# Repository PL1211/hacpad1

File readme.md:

XIAO RP2040 6-Key Macropad BOM

A simple 6-button macropad with rotary encoder, RGB LEDs, and OLED display running KMK firmware on CircuitPython. I made this to control my music easier with play/pause buttons and volume up, down, and mute.

1x Seeed XIAO RP2040

1x Header pins for the XIAO (usually included, do NOT solder the board flat)

6x Mechanical Switches (MX-Style)

1x EC11 Rotary Encoder (5-pin)

1x Knob for Encoder

6x Blank DSA Keycaps (White)

1x 0.91" OLED Display (Pin order must be GND-VCC-SCL-SDA)

6x SK6812 MINI-E LEDs (Reverse mount with legs)

7x 1N4148 Diodes (Through-Hole)

1x 3D Printed Case (PLA/PETG, not Acrylic)

4x M3 x 16mm Screws

4x M3 Heat-Set Inserts (M3x5mmx4mm)

Wire (24-28 AWG)

## Pictures

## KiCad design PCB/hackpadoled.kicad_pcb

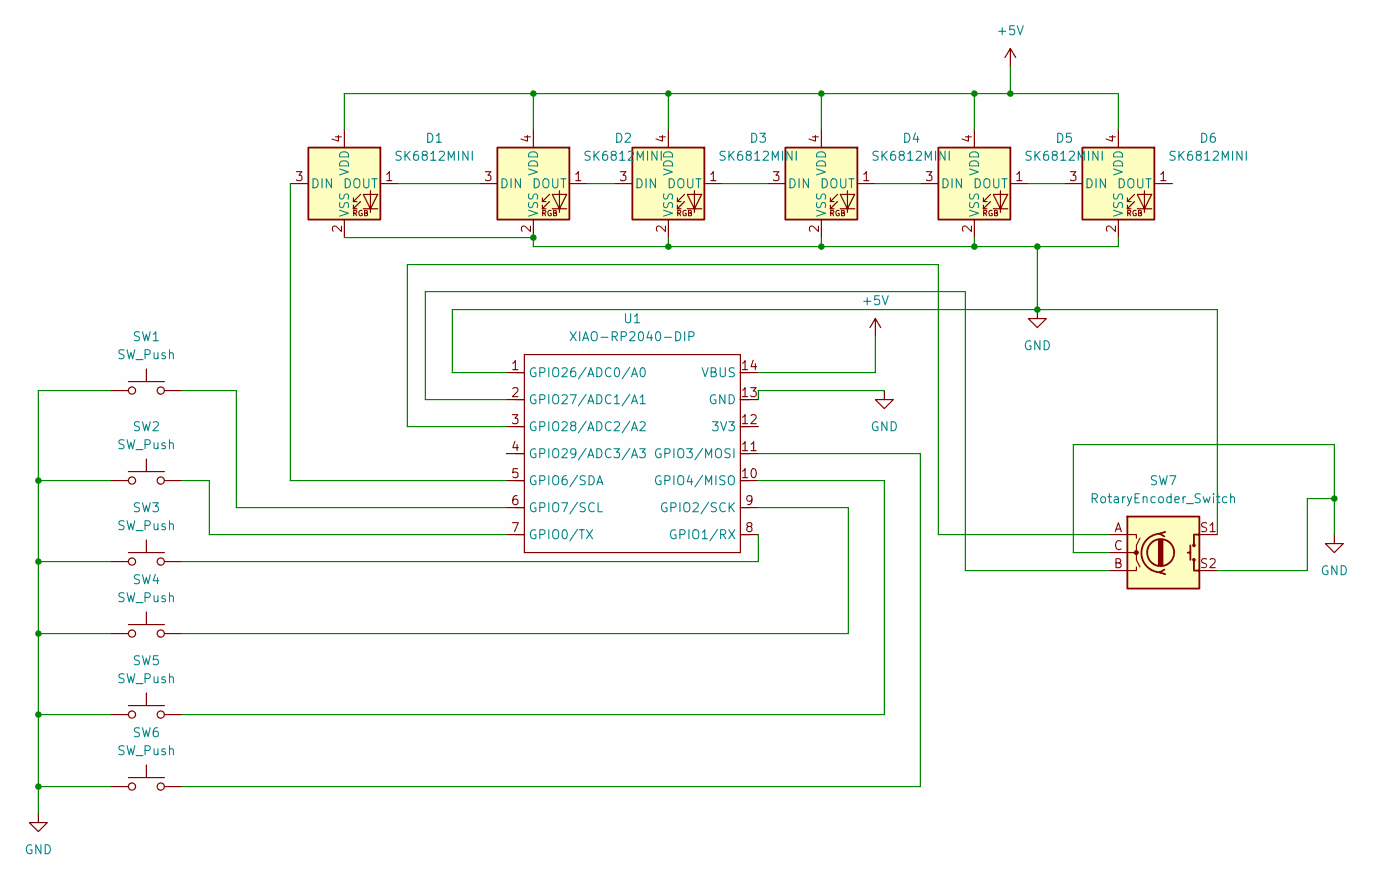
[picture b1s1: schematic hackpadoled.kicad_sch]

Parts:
D1, D2, D3, D4, D5, D6: SK6812MINI; LED_SK6812MINI_PLCC4_3.5x3.5mm_P1.75mm
SW1, SW2, SW3, SW4, SW5, SW6: SW_Push; SW_Cherry_MX_1.00u_PCB
SW7: RotaryEncoder_Switch; RotaryEncoder_Alps_EC11E-Switch_Vertical_H20mm
U1: XIAO-RP2040-DIP

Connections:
+5V: D1.4 (VDD), D2.4 (VDD), D3.4 (VDD), D4.4 (VDD), D5.4 (VDD), D6.4 (VDD), U1.14 (VBUS)
GND: D1.2 (VSS), D2.2 (VSS), D3.2 (VSS), D4.2 (VSS), D5.2 (VSS), D6.2 (VSS), SW1.1, SW2.1, SW3.1, SW4.1, SW5.1, SW6.1, SW7.C, SW7.S1, SW7.S2, U1.1 (GPIO26/ADC0/A0), U1.13 (GND)
unnamed: D1.3 (DIN), U1.5 (GPIO6/SDA)
unnamed: D1.1 (DOUT), D2.3 (DIN)
unnamed: D2.1 (DOUT), D3.3 (DIN)
unnamed: D3.1 (DOUT), D4.3 (DIN)
unnamed: D4.1 (DOUT), D5.3 (DIN)
unnamed: D5.1 (DOUT), D6.3 (DIN)
unnamed: SW2.2, U1.7 (GPIO0/TX)
unnamed: SW3.2, U1.8 (GPIO1/RX)
unnamed: SW4.2, U1.9 (GPIO2/SCK)
unnamed: SW6.2, U1.11 (GPIO3/MOSI)
unnamed: SW5.2, U1.10 (GPIO4/MISO)
unnamed: SW1.2, U1.6 (GPIO7/SCL)
unnamed: SW7.B, U1.2 (GPIO27/ADC1/A1)
unnamed: SW7.A, U1.3 (GPIO28/ADC2/A2)

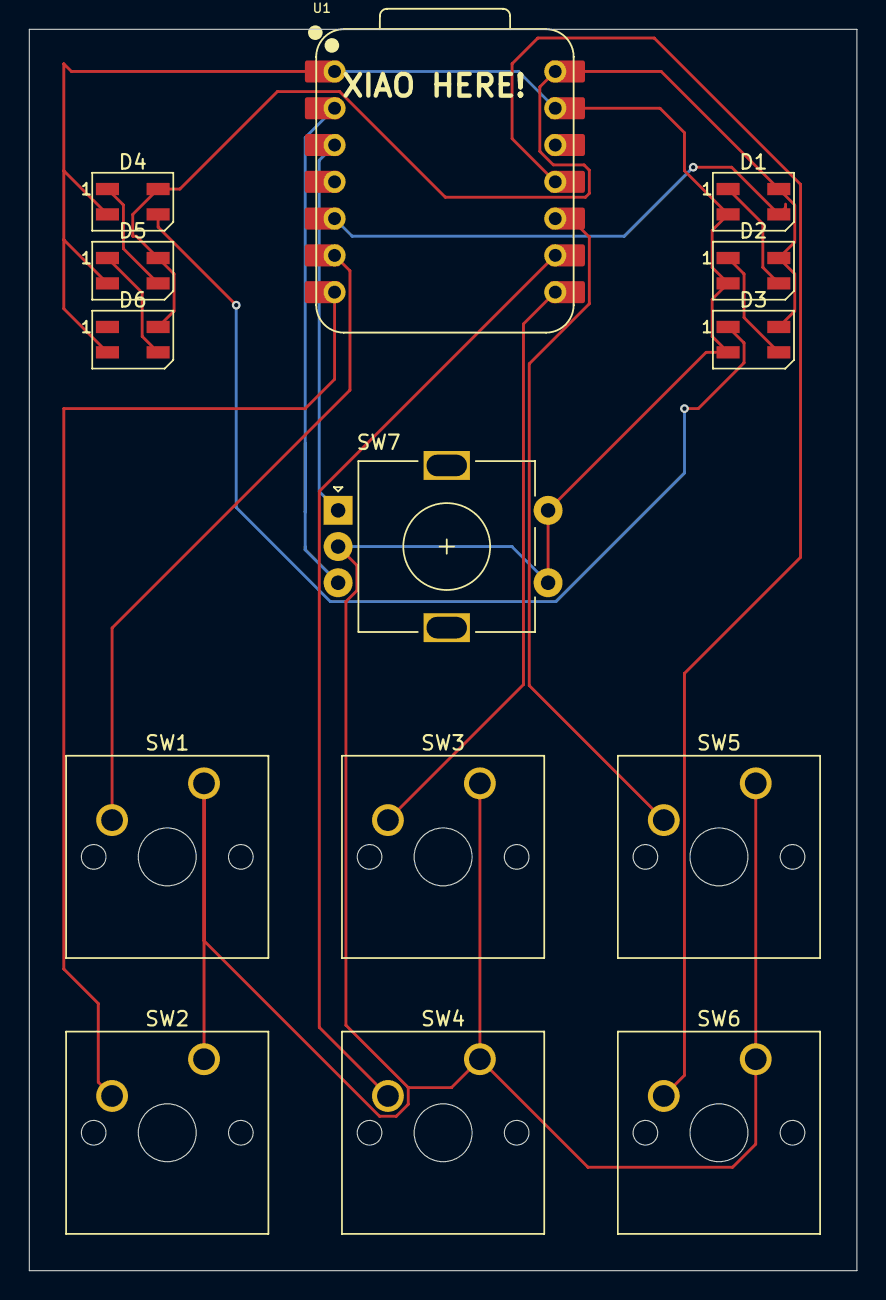
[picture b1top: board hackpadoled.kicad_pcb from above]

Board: 2 copper layers, 57.1 x 85.7 mm, 14 parts (0 on the bottom side), 16 nets.

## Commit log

2025-11-27 pictures and readme
2025-11-27 Initial plan
2025-11-27 Add all pictures from PICTURES folder to readme.md
2025-12-06 Update readme with macropad description
    Added a brief description of the XIAO RP2040 6-Key Macropad and its features.
2025-12-06 updated pictures title and summary
2025-12-07 picgture updatge
2025-12-07 updated cad and pictures
2025-12-09 updated pictures
